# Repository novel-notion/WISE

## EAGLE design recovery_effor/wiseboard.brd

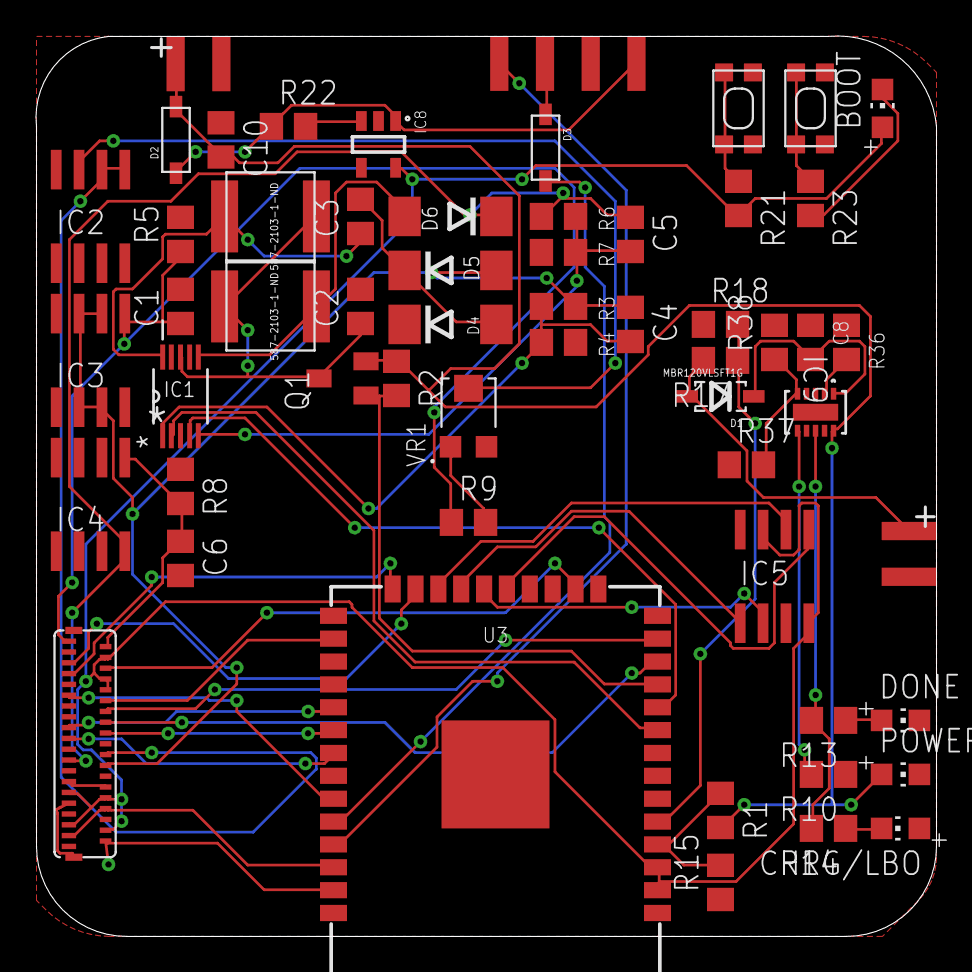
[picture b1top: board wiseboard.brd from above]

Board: 2 copper layers, 50.0 x 50.0 mm, 57 parts (0 on the bottom side), 58 nets.

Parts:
22: 587-2103-1-ND
BOOT: LED1; CHIP-LED0805
C1, C2, C3, C6: 1uF; C0805
C4, C5, C8, C10: 10uF; C0805
CHRG/LBO: LED3; CHIP-LED0805
D1: MBR120VLSFT1G; SOD-123
D2: MBR120; SOD-123
D3: 1n4148; SOD-123
D4, D5, D6: SS24; DO214AA
DONE: LED4; CHIP-LED0805
IC1: LT1945; SOP50P490X110-10N
IC2: LM358; SO08
IC3: L79L15; SO8
IC4: L78L15; SO8
IC5: W25Q; SO8
IC8: IC6; SOT95P280X145-5N
IC9: BQ24210DQCT; DQC10_P84X2P4
J1: BAT_CON; EDGE_CON_2
J2: SOL_CON; EDGE_CON_2
J3: PROG_HEADER; EDGE_CON_4
POWERGOOD: LED2; CHIP-LED0805
Q1: IRLM; SOT23
R1, R15, R17, R18, R21, R22: 10K; R0805
R2, R37: 10k; R0805
R3: 470k; R0805
R4, R5, R7, R8: 39k; R0805
R6: 560k; R0805
R9: 200k; R0805
R10, R13, R14, R23: 1K; R0805
R36: 790; R0805
R38: 7.6k; R0805
SW1, SW2: SPST_TACT-KMR2; KMR2
U3: ESP-WROOM-03
U$4: FH26W-39S; HFQ339CT-ND
U$5: 587-2103-1-ND
VR1: TC33X-104ECT-ND; TRIM_TC33X-2-103E

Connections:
+3V3: BOOT.A, IC5.3, IC5.8, IC8.5, R21.2, U3.2, U3.3, U$4.P$4, U$4.P$8, U$4.P$10, U$4.P$29, U$4.P$30, U$4.P$35, U$4.P$36
+15V: C6.1, IC4.1, R8.2, U$4.P$2
+22V: C5.1, D6.C, IC4.8, R6.2, U$4.P$23
-15V: C1.1, IC3.1, R5.1, R9.1, U$4.P$1
-20V: C4.1, D5.A, IC3.2, IC3.3, IC3.6, IC3.7, R3.2, U$4.P$24
BAT_SENS: R1.1, R15.2, U3.4
CKV: U3.37, U$4.P$33, U$4.P$38
CL: U3.23, U$4.P$5
CLK: IC5.6, U3.20
D0: U3.26, U$4.P$12
D1: U3.27, U$4.P$13
D2: U3.13, U$4.P$14
D3: U3.28, U$4.P$15
D4: U3.12, U$4.P$16
D5: U3.29, U$4.P$17
D6: U3.30, U$4.P$18
D7: U3.31, U$4.P$19
ESP_DI: IC5.2, U3.22
ESP_DO: IC5.5, U3.21
FB2: C5.2, IC1.5, R6.1, R7.2
GMODE: U$4.P$27, U$4.P$28
GND: C1.2, C2.2, C6.2, C8.1, C10.1, D4.C, DONE.C, IC1.3, IC1.7, IC1.9, IC3.5, IC4.2, IC4.3, IC4.6, IC4.7, IC5.4, IC8.2, IC9.3, IC9.7, IC9.11, J1.2, J2.2, J3.4, R4.1, R5.2, R7.1, R8.1, R15.1, R18.1, R36.1, R37.1, SW1.1, SW1.3, SW2.1, SW2.3, U3.1, U3.15, U3.38, U3.GND, U$4.GND@1, U$4.GND@2, U$4.P$3, U$4.P$9, U$4.P$31, U$4.P$34, VR1.3
GPIO0: R23.1, SW1.2, SW1.4
IC5: IC5.1, U3.19
LE: U3.16, U$4.P$6
unnamed: IC2.3, VR1.2
unnamed: 22.P$2, C3.1, IC1.10
unnamed: C8.2, D1.C, IC9.1
unnamed: 22.P$1, C2.1, IC1.8, Q1.3, U$5.P$2
unnamed: D6.A, IC1.6, U$5.P$1
unnamed: C3.2, D4.A, D5.C
unnamed: R9.2, VR1.1
unnamed: IC9.6, R10.2
unnamed: CHRG/LBO.C, R14.1
unnamed: POWERGOOD.C, R10.1
unnamed: DONE.A, R13.1
unnamed: IC9.8, R13.2, R14.2
unnamed: IC9.2, R36.2
unnamed: BOOT.C, R23.2
unnamed: IC8.3, R22.2
unnamed: IC9.5, R37.2, R38.1
unnamed: IC9.4, R38.2
NEGEN: IC1.2, U3.9
NFB1: C4.2, IC1.1, R3.1, R4.2
OE: U3.24, U$4.P$7
PANEL: D1.A, J2.1, R17.2
PANEL_SENS: R17.1, R18.2, U3.5
POSEN: IC1.4, U3.10
RESET: R21.1, SW2.2, SW2.4
RXD: D3.A, U3.34
RXD_5V: D3.C, J3.2
SPH: U3.33, U$4.P$11
SPV: U3.36, U$4.P$32, U$4.P$37
SUP_CTRL: Q1.1, R2.2, U3.11
TXD: J3.1, U3.35
VBAT: C10.2, CHRG/LBO.A, D2.A, IC9.10, J1.1, POWERGOOD.A, Q1.2, R1.2, R2.1
VCC: D2.C, IC8.1, J3.3, R22.1
VCOMMON: IC2.1, IC2.2, U$4.P$22
